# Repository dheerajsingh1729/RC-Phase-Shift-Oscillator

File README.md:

# RC-Phase-Shift-Oscillator

# RC Phase Shift Oscillator

This repository contains the KiCad design files for a 1 kHz RC Phase Shift Oscillator built using an operational amplifier. The circuit uses a three-section RC feedback network to generate a sinusoidal output waveform.

## Overview

An RC Phase Shift Oscillator produces oscillations by using a resistor-capacitor ladder network to create a total phase shift of 180 degrees. An inverting amplifier adds another 180 degrees, making the total loop phase shift 360 degrees. This satisfies the Barkhausen criterion for sustained oscillation.

The design is targeted for approximately 1 kHz.

## Circuit Principle

The oscillation frequency for a three-section RC phase shift oscillator is:

```text
f0 = 1 / (2πRC√6)
For this design:

R = 10 kΩ
C = 16 nF
Therefore:

f0 ≈ 1020 Hz ≈ 1 kHz
The minimum amplifier gain required for oscillation is approximately:

|Av| ≥ 29
Therefore, the feedback resistor is selected as:

Rf = 29R ≈ 290 kΩ
Components Used
Component	Value / Part	Quantity
Op-Amp	LM741	1
Resistor	10 kΩ	3
Capacitor	16 nF	3
Feedback Resistor	290 kΩ	1
Power Supply	±12 V DC	1
Repository Contents
RC-Phase-Shift-Oscillator/
├── Rc oscillator.kicad_pro
├── Rc oscillator.kicad_sch
├── Rc oscillator.kicad_pcb
├── Rc oscillator.kicad_prl
├── Rc oscillator-backups/
├── fp-info-cache
└── README.md
Features
1 kHz sine wave oscillator design
Three-section RC phase shift feedback network
Op-amp based inverting amplifier
PCB layout designed in KiCad
Suitable for analog electronics laboratory experiments
Tools Used
KiCad for schematic and PCB design
LM741 op-amp for oscillator implementation
Oscilloscope for waveform verification
Expected Output
The circuit is expected to generate a sinusoidal waveform of approximately 1 kHz when powered using a dual DC supply.

Output waveform: Sine wave
Expected frequency: ~1 kHz
Supply voltage: ±12 V DC
Applications
Audio-frequency signal generation
Analog electronics laboratory experiments
Op-amp oscillator demonstration
RC network frequency analysis
PCB design practice using KiCad
References
D. Roy Choudhury, Linear Circuit Analysis and Design
R. A. Gayakwad, Op-Amps and Linear Integrated Circuits
A. S. Sedra and K. C. Smith, Microelectronic Circuits
Author
Dheeraj Singh
Department of Electronics and Communication Engineering
Central University of Rajasthan
Email: 2022btece004@curaj.ac.in

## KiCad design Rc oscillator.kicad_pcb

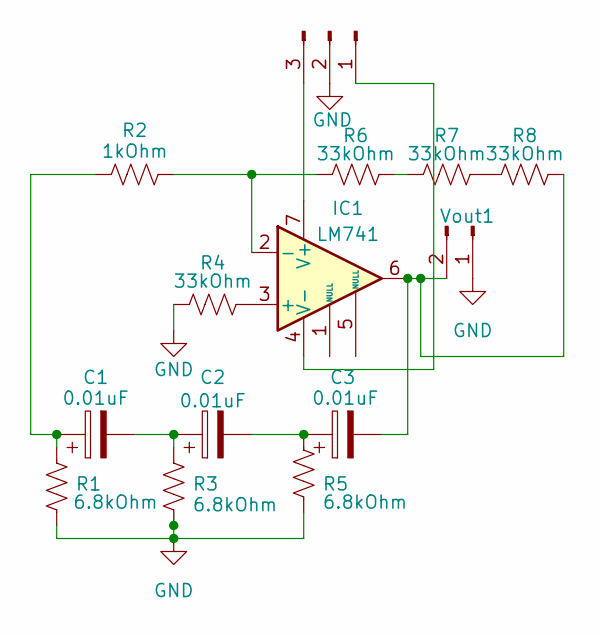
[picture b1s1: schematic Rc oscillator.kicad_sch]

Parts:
C1, C2, C3: 0.01uF; CP_Radial_D4.0mm_P2.00mm
IC1: LM741; DIP775W46P254L1016H508Q8
J1: Conn_01x03_Pin; PinHeader_1x03_P2.54mm_Vertical
R1, R3, R5: 6.8kOhm; R_Axial_DIN0207_L6.3mm_D2.5mm_P7.62mm_Horizontal
R2: 1kOhm; R_Axial_DIN0207_L6.3mm_D2.5mm_P7.62mm_Horizontal
R4, R6, R7, R8: 33kOhm; R_Axial_DIN0207_L6.3mm_D2.5mm_P7.62mm_Horizontal
Vout1: Conn_01x02_Pin; PinHeader_1x02_P2.54mm_Vertical

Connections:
GND: J1.2 (GND), R1.2, R3.2, R4.1, R5.2, Vout1.1
unnamed: C1.1, R1.1, R2.1
unnamed: C1.2, C2.1, R3.1
unnamed: C2.2, C3.1, R5.1
unnamed: IC1.3 (+), R4.2
unnamed: IC1.2 (-), R2.2, R6.1
unnamed: IC1.7 (V+), J1.3 (+Vcc)
unnamed: IC1.4 (V-), J1.1 (-VCC)
unnamed: R6.2, R7.1
unnamed: R7.2, R8.1
unnamed: C3.2, IC1.6, R8.2, Vout1.2

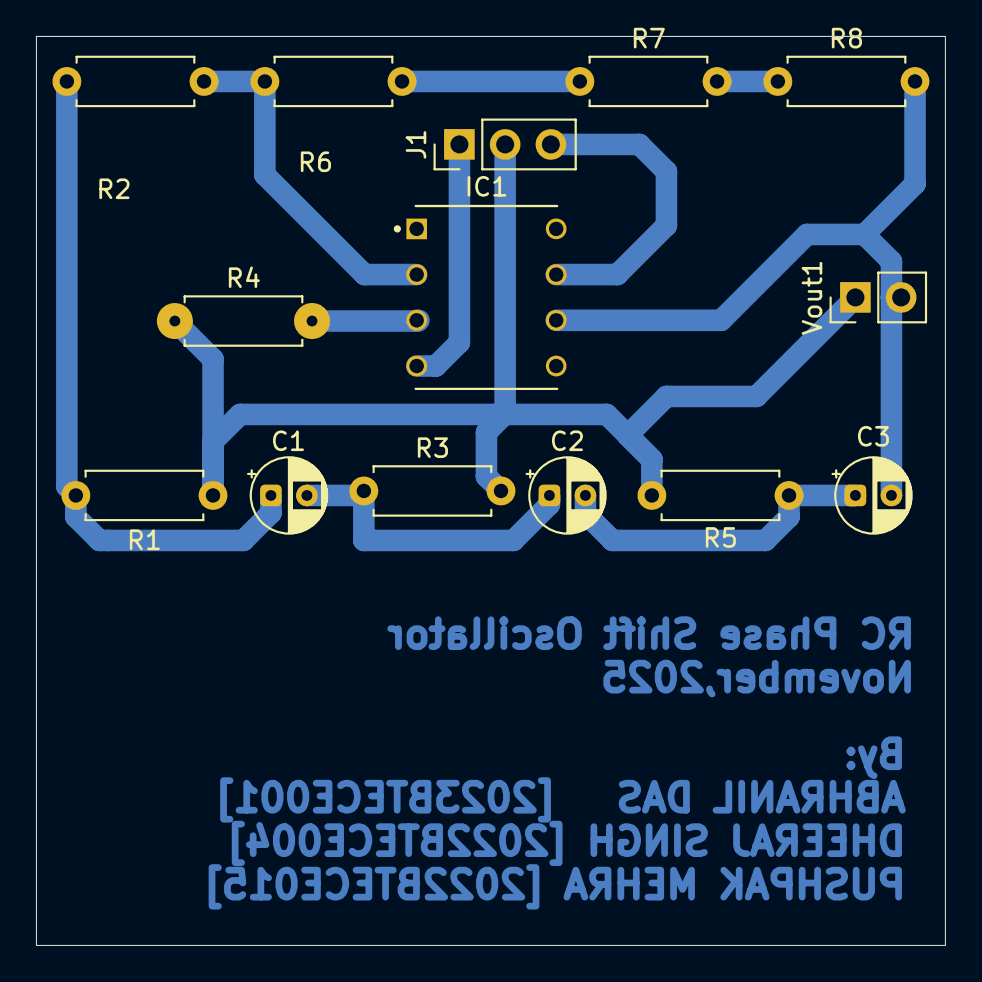
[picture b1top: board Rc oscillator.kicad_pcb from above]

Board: 2 copper layers, 50.5 x 50.5 mm, 14 parts (0 on the bottom side), 11 nets.
